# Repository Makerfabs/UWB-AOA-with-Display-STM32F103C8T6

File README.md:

# UWB-AOA-with-Display-STM32F103C8T6

UWB AOA with Display STM32F103C8T6

# Makerfabs

[Makerfabs Homepage](https://www.makerfabs.com/)

[Makerfabs Wiki](https://wiki.makerfabs.com/)

# Feature:

• Controller: STM32F103C8T6, max 72MHz frequency, 1.25 DMIPS/MHz(Dhrystone 2.1), 64KB Flash memory, 20KB SRAM  

• DW3000 Module(Anchor):UWB-X3-AOA  

• DW3000 Module(Tag):UWB-X3-MAX  

• OLED: 1.3" SSD1306, 128X64, I2C  

• "Zero" Dropout: On board ideal diode circuit  

• Dual-USB Type C:USB-Native/USB-TTL  

• USB-to-UART: CH340K  

• Charger: TP4056  

• Button:RST/BTN  

• Expander: 2X12 2.54mm header  

• Open Source: hardware/firmware/software  

• Coverage radius: 30m@6.8M 

• angle:+/-60° 

• angle error:±5° 

• Ranging error:< 10cm 

• Positioning error： <10cm 

• Frequency: CH5 (6.5 GHz)/CH9 (8 GHz)  

• Speed rate: 850 Kbps/6.8Mbps  

• Communication interface: SPI  

• Power Supply: USB 5.0V or 3.7V lithium battery  

# Usage:

1. Insert to USB-NATIVE port of AOA anchor.  
2. Insert to USB-TTL port of AOA tag(Or Powered by Li-battery).  
3. Open the AOA System Application.  
4. Select Tag ID and joined.  
5. Result Show:  

# Firmware

| Type | Default Firmware | 
|---|---|
| Anchor | Project\_Anchor\_v1.0.hex |
| Tag | Project\_Tag\_v1.0.hex |

# How to Program?

|ST-LINK V2 |AOA Anchor/Tag Board|  
| ---- | ---- | 
|SWCLK|SWCK|  
|SWDIO|SWIO|  
|GND|GND|  
|3.3V|+3.3V|  

# How to turn on the PA in tag?
1. Modify the value of PMSC_TXFINESEQ_DISABLE to 0x0d20010 in deca_vals.h header file: 

#define PMSC_TXFINESEQ_DISABLE  0x0d20010 

2. Add a definition in config_options.h header file: 

#define HW_PA 

# Why there is No com port in AOA system software?  

1. Install the STM32_VCP_V1.4.0_Setup.exe in Driver folder.  
2. Update the driver from the Device Manager.  
3. Insert the USB Type C cable to USB Native port of AOA Anchor before you open the AOA system software. 

# Where to purchase? 
[AOA KIT](https://www.makerfabs.com/mauwb-stm32-aoa-development-kit.html) 

# FAQ

You can list your question here or contact techsupport@makerfabs.com for technology support. Detailed descriptions of your question will be helped to solve your question.

• Q:The AOA kit has multiple tag bindings, resulting in the inability to obtain distance and angle information.

• A:One AOA device only supports one anchor point paired with one tag to work simultaneously. Excess tags will cause the data not to be displayed. Please unbind the phantom false tags in the interface, and the kit can be used normally.

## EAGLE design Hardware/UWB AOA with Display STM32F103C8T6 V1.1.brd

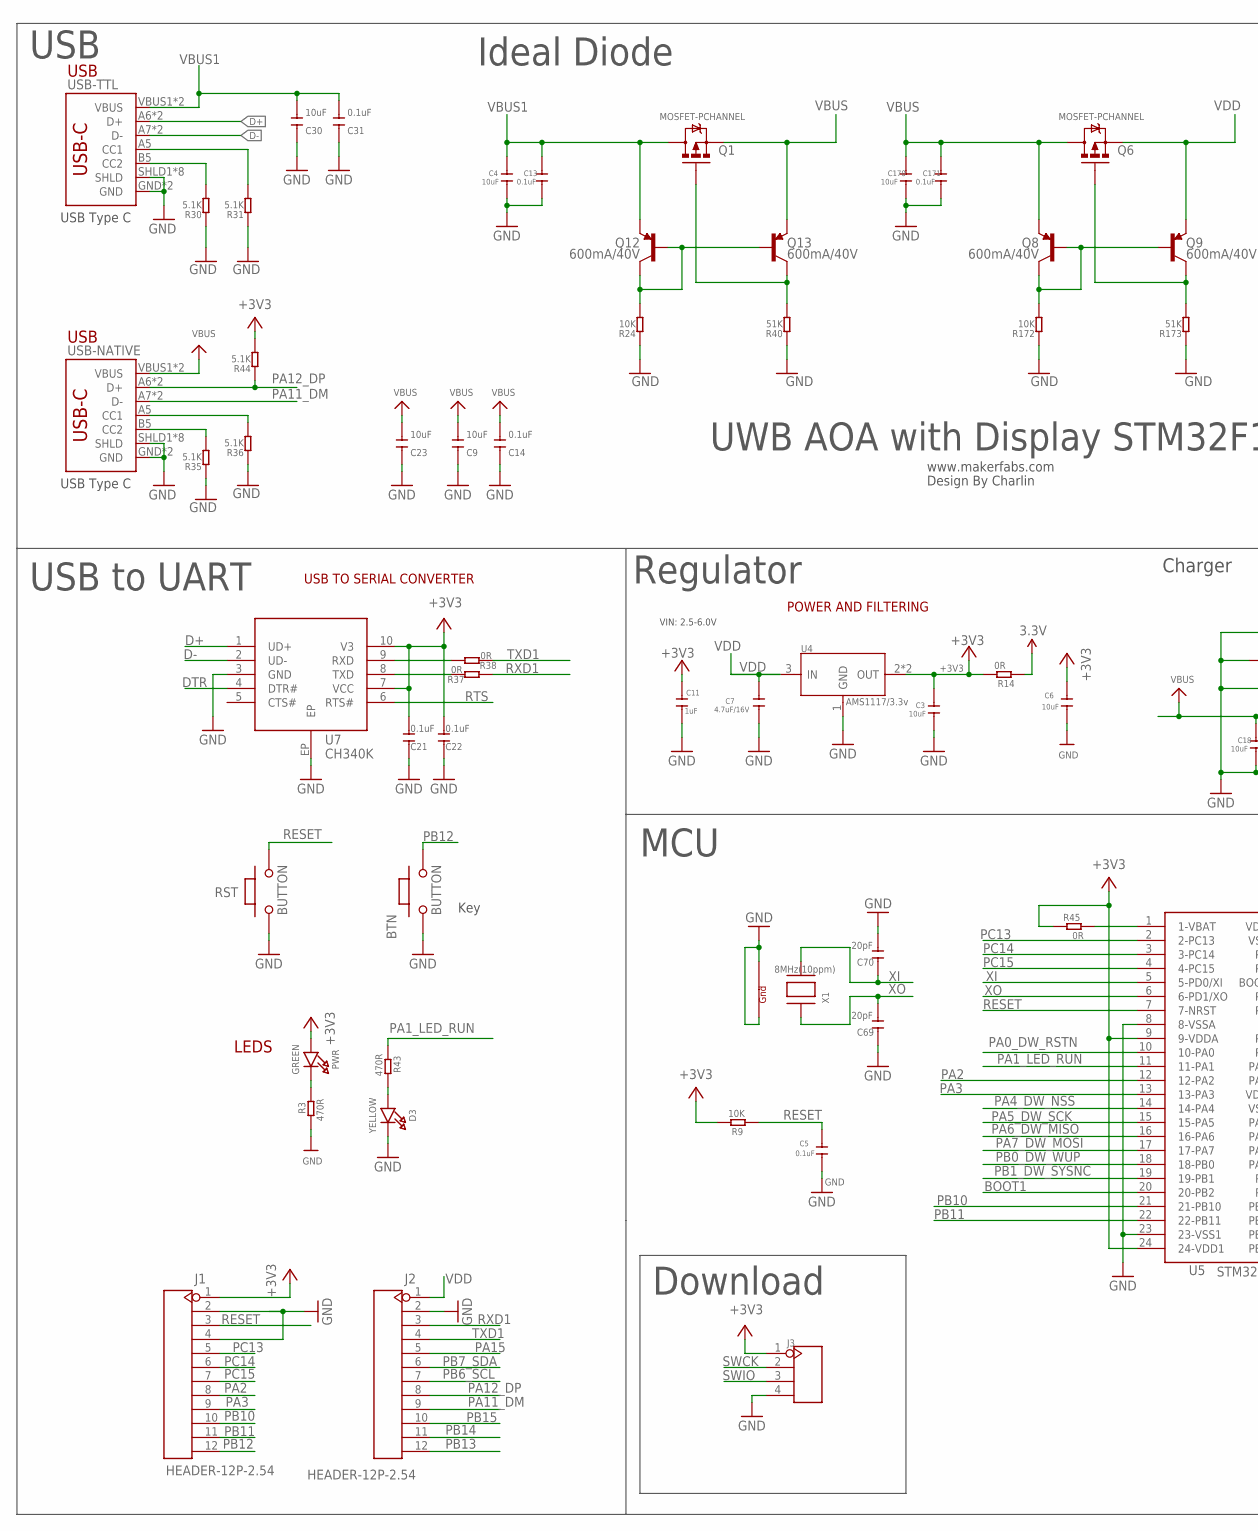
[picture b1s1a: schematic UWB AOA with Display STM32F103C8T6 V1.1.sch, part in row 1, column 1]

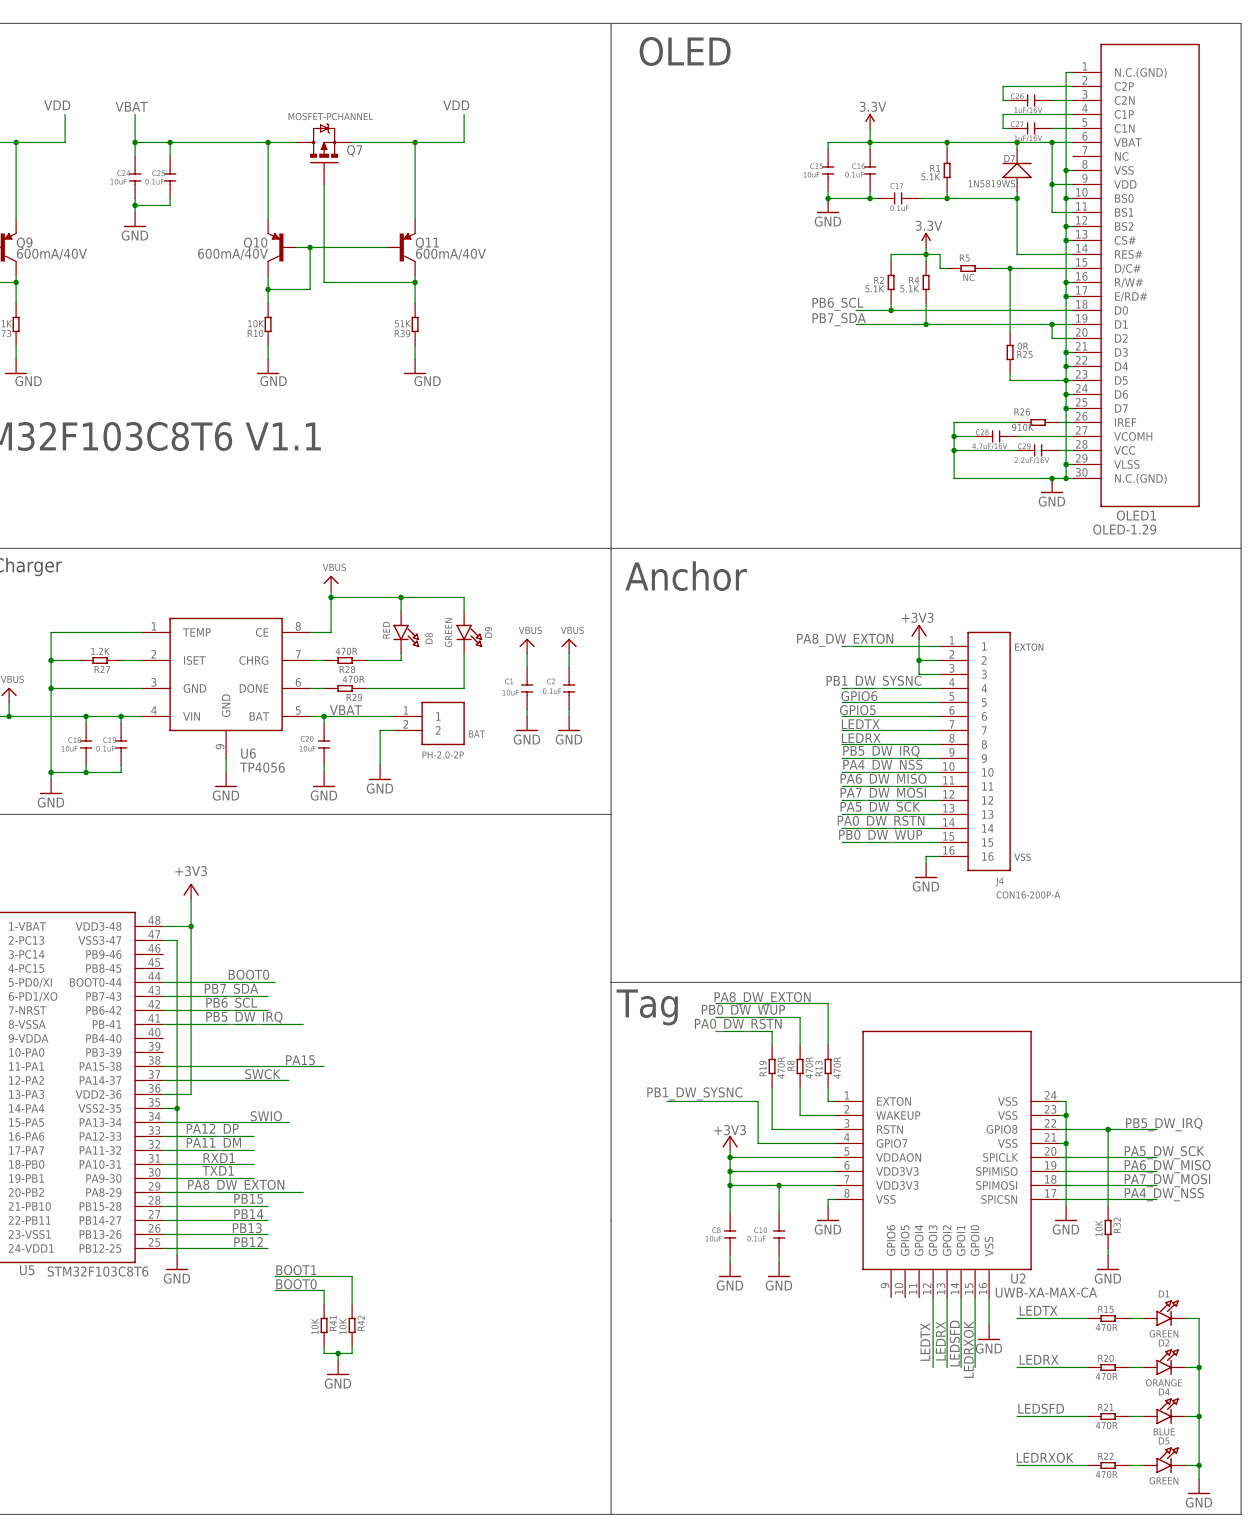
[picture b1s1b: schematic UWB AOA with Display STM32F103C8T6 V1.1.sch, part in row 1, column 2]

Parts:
BAT: PH-2.0-2P
BTN: BUTTON; 157SW
C1, C3, C4, C6, C8, C15, C18, C20, C24, C170: 10uF; C0603
C2, C5, C10, C13, C16, C17, C19, C25, C171: 0.1uF; C0603
C7, C28: 4.7uF/16V; C0603
C9, C23, C30: 10uF; DISCRETE_C0603
C11: 1uF; C0603
C14, C21, C22, C31: 0.1uF; DISCRETE_C0603
C26, C27: 1uF/16V; C0603
C29: 2.2uF/16V; C0603
C69, C70: 20pF; DISCRETE_C0402
D1, D5, D9: GREEN; CHIPLED_0805_NOOUTLINE
D2: ORANGE; CHIPLED_0805_NOOUTLINE
D3: YELLOW; CHIPLED_0805_NOOUTLINE
D4: BLUE; CHIPLED_0805_NOOUTLINE
D7: 1N5819WS; SOD323
D8: RED; CHIPLED_0805_NOOUTLINE
J1, J2: HEADER-12P-2.54; 12P-2.54
J3: HEADER-4P-60/35MILROUND; 4P-65/35ROUND
J4: CON16-200P-A; THD16-200P-3250L240W430H
OLED1: OLED-1.29
PWR: GREEN; CHIPLED_0805_NOOUTLINE
Q1, Q6, Q7: MOSFET-PCHANNEL; SOT23-3
Q8, Q9, Q10, Q11, Q12, Q13: 600mA/40V; SOT23-3
R1, R2, R4: 5.1K; R0603
R3, R8, R13, R15, R19, R20, R21, R22, R28, R29, R43: 470R; R0603
R5: NC; R0603
R9, R32, R41, R42: 10K; R0603
R10, R24, R172: 10K; DISCRETE_R0603
R14, R25, R37, R38, R45: 0R; R0603
R26: 910K; R0603
R27: 1.2K; R0603
R30, R31, R35, R36, R44: 5.1K; DISCRETE_R0603
R39, R40, R173: 51K; DISCRETE_R0603
RST: BUTTON; 157SW
U2: UWB-XA-MAX-CA; UWB-X1-MAK-CA
U4: AMS1117/3.3v; SOT89
U5: STM32F103C8T6; LQFP48-50P-900L900W160H
U6: TP4056; SOP8-1.27P
U7: CH340K; ESOP-10-EP-150MIL
USB-NATIVE: USB_C5; USB-C-16P-5
USB-TTL: USB_C5; USB-C-16P-5
X1: 8MHz(10ppm); NX3225

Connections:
3.3V: C15.1, C16.1, D7.-, OLED1.6 (VBAT), OLED1.9 (VDD), OLED1.11 (BS1), R1.2, R2.2, R4.2, R5.2, R14.1
+3V3: C3.1, C6.1, C8.1, C10.1, C11.1, C21.2, C22.2, J1.1, J3.1, J4.2, J4.3, PWR.A, R9.2, R14.2, R44.2, R45.1, U2.5 (VDDAON), U2.6 (VDD3V3), U2.7 (VDD3V3), U4.2 (OUT), U4.4 (OUT), U5.9 (9-VDDA), U5.24 (24-VDD1), U5.36 (VDD2-36), U5.48 (VDD3-48), U7.7 (VCC), U7.10 (V3)
BOOT0: R41.1, U5.44 (BOOT0-44)
BOOT1: R42.1, U5.20 (20-PB2)
D+: U7.1 (UD+), USB-TTL.A6 (D+), USB-TTL.B6 (D+)
D-: U7.2 (UD-), USB-TTL.A7 (D-), USB-TTL.B7 (D-)
DTR: U7.4 (DTR#)
GND: BAT.2, BTN.1, C1.2, C2.2, C3.2, C4.2, C5.2, C6.2, C7.2, C8.2, C9.1, C10.2, C11.2, C13.2, C14.1, C15.2, C16.2, C17.1, C18.2, C19.2, C20.2, C21.1, C22.1, C23.1, C24.2, C25.2, C28.1, C29.1, C30.1, C31.1, C69.2, C70.1, C170.2, C171.2, D1.C, D2.C, D3.C, D4.C, D5.C, J1.2, J1.4, J2.2, J3.4, J4.16, OLED1.1 (N.C.(GND)), OLED1.8 (VSS), OLED1.10 (BS0), OLED1.12 (BS2), OLED1.13 (CS#), OLED1.16 (R/W#), OLED1.17 (E/RD#), OLED1.21 (D3), OLED1.22 (D4), OLED1.23 (D5), OLED1.24 (D6), OLED1.25 (D7), OLED1.29 (VLSS), OLED1.30 (N.C.(GND)), R3.1, R10.1, R24.1, R25.2, R26.2, R27.2, R30.1, R31.1, R32.2, R35.1, R36.1, R39.1, R40.1, R41.2, R42.2, R172.1, R173.1, RST.1, U2.8 (VSS), U2.16 (VSS), U2.21 (VSS), U2.23 (VSS), U2.24 (VSS), U4.1 (GND), U5.8 (8-VSSA), U5.23 (23-VSS1), U5.35 (VSS2-35), U5.47 (VSS3-47), U6.1 (TEMP), U6.3 (GND), U6.9 (GND), U7.3 (GND), U7.EP, USB-NATIVE.GND, USB-NATIVE.GND2 (GND), USB-NATIVE.SHLD1 (SHLD), USB-NATIVE.SHLD2 (SHLD), USB-NATIVE.SHLD3 (SHLD), USB-NATIVE.SHLD4 (SHLD), USB-NATIVE.SHLD5 (SHLD), USB-NATIVE.SHLD6 (SHLD), USB-NATIVE.SHLD7 (SHLD), USB-NATIVE.SHLD8 (SHLD), USB-TTL.GND, USB-TTL.GND2 (GND), USB-TTL.SHLD1 (SHLD), USB-TTL.SHLD2 (SHLD), USB-TTL.SHLD3 (SHLD), USB-TTL.SHLD4 (SHLD), USB-TTL.SHLD5 (SHLD), USB-TTL.SHLD6 (SHLD), USB-TTL.SHLD7 (SHLD), USB-TTL.SHLD8 (SHLD), X1.2 (G2), X1.4 (G1)
GPIO5: J4.6
GPIO6: J4.5
LEDRX: J4.8, R20.1, U2.13 (GPOI2)
LEDRXOK: R22.1, U2.15 (GPOI0)
LEDSFD: R21.1, U2.14 (GPOI1)
LEDTX: J4.7, R15.1, U2.12 (GPOI3)
unnamed: D1.A, R15.2
unnamed: C17.2, D7.+, OLED1.14 (RES#), R1.1
unnamed: OLED1.15 (D/C#), R5.1, R25.1
unnamed: PWR.C, R3.2
unnamed: C28.2, OLED1.27 (VCOMH)
unnamed: C26.2, OLED1.3 (C2N)
unnamed: C29.2, OLED1.28 (VCC)
unnamed: OLED1.26 (IREF), R26.1
unnamed: R13.1, U2.1 (EXTON)
unnamed: R8.1, U2.2 (WAKEUP)
unnamed: R19.1, U2.3 (RSTN)
unnamed: Q10.1 (B), Q10.3 (C), Q11.1 (B), R10.2
unnamed: D2.A, R20.2
unnamed: D4.A, R21.2
unnamed: D5.A, R22.2
unnamed: C26.1, OLED1.2 (C2P)
unnamed: C27.1, OLED1.4 (C1P)
unnamed: C27.2, OLED1.5 (C1N)
unnamed: R27.1, U6.2 (ISET)
unnamed: D3.A, R43.2
unnamed: R31.2, USB-TTL.A5 (CC1)
unnamed: R30.2, USB-TTL.B5 (CC2)
unnamed: R45.2, U5.1 (1-VBAT)
unnamed: R28.2, U6.7 (CHRG)
unnamed: R29.2, U6.6 (DONE)
unnamed: D8.C, R28.1
unnamed: D9.C, R29.1
unnamed: R36.2, USB-NATIVE.A5 (CC1)
unnamed: R35.2, USB-NATIVE.B5 (CC2)
unnamed: Q7.1 (G), Q11.3 (C), R39.2
unnamed: Q12.1 (B), Q12.3 (C), Q13.1 (B), R24.2
unnamed: Q1.1 (G), Q13.3 (C), R40.2
unnamed: R38.2, U7.9 (RXD)
unnamed: R37.2, U7.8 (TXD)
unnamed: Q8.1 (B), Q8.3 (C), Q9.1 (B), R172.2
unnamed: Q6.1 (G), Q9.3 (C), R173.2
PA0_DW_RSTN: J4.14, R19.2, U5.10 (10-PA0)
PA1_LED_RUN: R43.1, U5.11 (11-PA1)
PA2: J1.8, U5.12 (12-PA2)
PA3: J1.9, U5.13 (13-PA3)
PA4_DW_NSS: J4.10, U2.17 (SPICSN), U5.14 (14-PA4)
PA5_DW_SCK: J4.13, U2.20 (SPICLK), U5.15 (15-PA5)
PA6_DW_MISO: J4.11, U2.19 (SPIMISO), U5.16 (16-PA6)
PA7_DW_MOSI: J4.12, U2.18 (SPIMOSI), U5.17 (17-PA7)
PA8_DW_EXTON: J4.1, R13.2, U5.29 (PA8-29)
PA11_DM: J2.9, U5.32 (PA11-32), USB-NATIVE.A7 (D-), USB-NATIVE.B7 (D-)
PA12_DP: J2.8, R44.1, U5.33 (PA12-33), USB-NATIVE.A6 (D+), USB-NATIVE.B6 (D+)
PA15: J2.5, U5.38 (PA15-38)
PB0_DW_WUP: J4.15, R8.2, U5.18 (18-PB0)
PB1_DW_SYSNC: J4.4, U2.4 (GPIO7), U5.19 (19-PB1)
PB5_DW_IRQ: J4.9, R32.1, U2.22 (GPIO8), U5.41 (PB-41)
PB6_SCL: J2.7, OLED1.18 (D0), R2.1, U5.42 (PB6-42)
PB7_SDA: J2.6, OLED1.19 (D1), OLED1.20 (D2), R4.1, U5.43 (PB7-43)
PB10: J1.10, U5.21 (21-PB10)
PB11: J1.11, U5.22 (22-PB11)
PB12: BTN.2, J1.12, U5.25 (PB12-25)
PB13: J2.12, U5.26 (PB13-26)
PB14: J2.11, U5.27 (PB14-27)
PB15: J2.10, U5.28 (PB15-28)
PC13: J1.5, U5.2 (2-PC13)
PC14: J1.6, U5.3 (3-PC14)
PC15: J1.7, U5.4 (4-PC15)
RESET: C5.1, J1.3, R9.1, RST.2, U5.7 (7-NRST)
RTS: U7.6 (RTS#)
RXD1: J2.3, R37.1, U5.31 (PA10-31)
SWCK: J3.2, U5.37 (PA14-37)
SWIO: J3.3, U5.34 (PA13-34)
TXD1: J2.4, R38.1, U5.30 (PA9-30)
VBAT: BAT.1, C20.1, C24.1, C25.1, Q7.3 (D), Q10.2 (E), U6.5 (BAT)
VBUS: C1.1, C2.1, C9.2, C14.2, C18.1, C19.1, C23.2, C170.1, C171.1, D8.A, D9.A, Q1.2 (S), Q6.3 (D), Q8.2 (E), Q13.2 (E), U6.4 (VIN), U6.8 (CE), USB-NATIVE.VBUS1 (VBUS), USB-NATIVE.VBUS2 (VBUS)
VBUS1: C4.1, C13.1, C30.2, C31.2, Q1.3 (D), Q12.2 (E), USB-TTL.VBUS1 (VBUS), USB-TTL.VBUS2 (VBUS)
VDD: C7.1, J2.1, Q6.2 (S), Q7.2 (S), Q9.2 (E), Q11.2 (E), U4.3 (IN)
XI: C70.2, U5.5 (5-PD0/XI), X1.3 (X2)
XO: C69.1, U5.6 (6-PD1/XO), X1.1 (X1)

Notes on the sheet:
Anchor
LEDS
POWER AND FILTERING
Key
UWB AOA with Display STM32F103C8T6 V1.1
VIN: 2.5-6.0V
USB
USB Type C
USB TO SERIAL CONVERTER
USB to UART
Tag
OLED
Charger
Ideal Diode
MCU
Regulator
Download
www.makerfabs.com
Design By Charlin

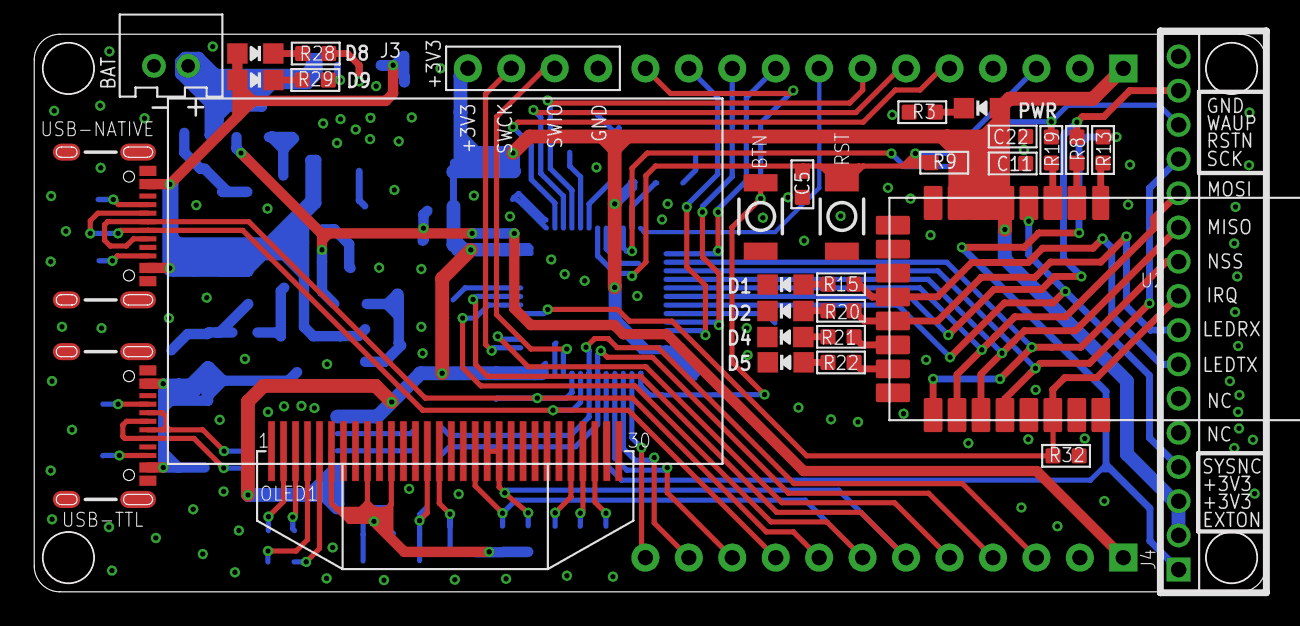
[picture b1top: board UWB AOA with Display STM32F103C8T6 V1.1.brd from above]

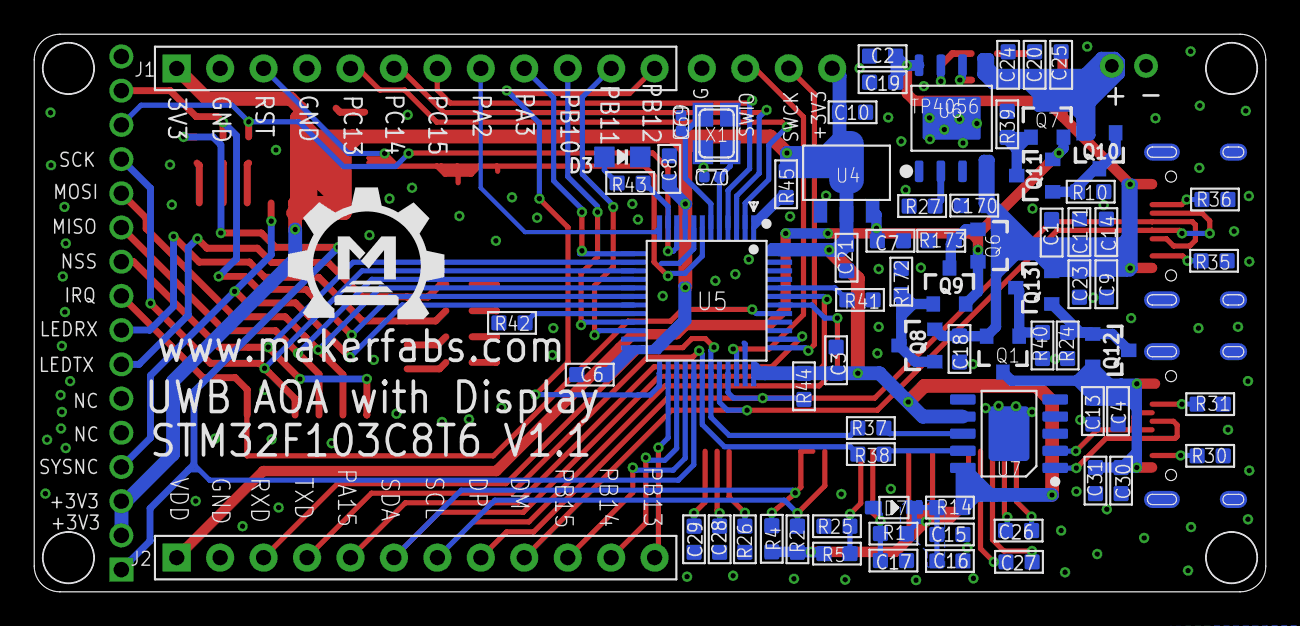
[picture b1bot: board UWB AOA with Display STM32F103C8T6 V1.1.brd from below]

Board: 2 copper layers, 72.0 x 32.6 mm, 106 parts (75 on the bottom side), 84 nets.

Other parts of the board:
U$1: MAKERFABS_0.3

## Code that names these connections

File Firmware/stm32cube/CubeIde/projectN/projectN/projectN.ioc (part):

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Mcu.Name=STM32F103C(8-B)Tx
Mcu.Package=LQFP48
Mcu.UserName=STM32F103C8Tx
PA1.GPIOParameters=PinState,GPIO_PuPd,GPIO_Label
PA1.GPIO_Label=LED0
PA1.GPIO_PuPd=GPIO_PULLUP
PA1.PinState=GPIO_PIN_SET
PA1.Signal=GPIO_Output
PA10.Mode=Asynchronous
PA10.Signal=USART1_RX
PA11.Mode=Device
PA11.Signal=USB_DM
PA12.Mode=Device
PA12.Signal=USB_DP
PA13.Mode=Serial_Wire
PA13.Signal=SYS_JTMS-SWDIO
PA14.Mode=Serial_Wire
PA14.Signal=SYS_JTCK-SWCLK
PA4.GPIOParameters=GPIO_Speed,PinState,GPIO_PuPd,GPIO_Label
PA4.GPIO_Label=DW1000_CS
PA4.GPIO_PuPd=GPIO_NOPULL
PA4.GPIO_Speed=GPIO_SPEED_FREQ_HIGH
PA4.PinState=GPIO_PIN_SET
PA4.Signal=GPIO_Output
PA5.Mode=Full_Duplex_Master
PA5.Signal=SPI1_SCK
PA6.Mode=Full_Duplex_Master
PA6.Signal=SPI1_MISO
PA7.Mode=Full_Duplex_Master
PA7.Signal=SPI1_MOSI
PA9.Mode=Asynchronous
PA9.Signal=USART1_TX
PB5.GPIOParameters=GPIO_PuPd,GPIO_ModeDefaultEXTI
PB5.GPIO_ModeDefaultEXTI=GPIO_MODE_IT_RISING
PB5.GPIO_PuPd=GPIO_PULLDOWN
PB5.Signal=GPXTI5
PB6.Mode=I2C
PB6.Signal=I2C1_SCL
PB7.Mode=I2C
PB7.Signal=I2C1_SDA
PC14-OSC32_IN.Mode=LSE-External-Oscillator
PC14-OSC32_IN.Signal=RCC_OSC32_IN
PC15-OSC32_OUT.Mode=LSE-External-Oscillator
PC15-OSC32_OUT.Signal=RCC_OSC32_OUT
PD0-OSC_IN.Mode=HSE-External-Oscillator
PD0-OSC_IN.Signal=RCC_OSC_IN
PD1-OSC_OUT.Mode=HSE-External-Oscillator
PD1-OSC_OUT.Signal=RCC_OSC_OUT
RCC.SYSCLKFreq_VALUE=72000000
RCC.SYSCLKSource=RCC_SYSCLKSOURCE_PLLCLK
board=custom

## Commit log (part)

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2025-08-21 Add hardware/Firmware/software
2025-08-21 Add Source Project of Tag and Anchor
    Opened by Keil5
2025-08-22 Add STM32 Virtual Com Port Driver and CH340 Driver
2025-09-01 Turn on Tag PA
2025-09-01 Turn on the PA firmware in TAG
2025-09-02 Add Doc of UWB-X3
2026-01-22 add stm32cubeide project code
2026-04-20 Add cube code
2026-04-20 Update table of contents

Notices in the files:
parts and their libraries:
microbuilder: This work is placed in the public domain, and may be freely used for commercial and non-commercial work with the following conditions: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
User-Submitted: Licensing: Creative Commons ShareAlike 4.0 International - https://creativecommons.org/licenses/by-sa/4.0
